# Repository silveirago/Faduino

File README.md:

# Faduino

The Faduino is a DIY MIDI controller inspired in the Presonus Faderport. It has one motorized fader, a rotary encoder and several silicone buttons, plus two PCBs. One PCB contains all the pads, which are triggered by the silicone buttons, addressable LEDs, a multiplexer, and some other stuff.
It can control natively any DAW, because it works with the MCU - or Mackie - Protocol, so it can work even in Pro Tools. With its motorized fader, rotary encoder, and LED buttons, you can change the track and the parameters in DAW get updated in the controller, moving the motorized fader, changing LEDs, etc.
With the Faduino you can control any channel strip, transport, and many other things in the DAW!

Complete Tutorial: Nerd Musician Pro (all the courses): https://go.musiconerd.com/nerd-musician-pro
Tutorialo Completo (Português): Fazendo Música com Arduino: https://go.musiconerd.com/fazendo-musica-com-arduino
Watch the YT video: https://youtu.be/M8krxn_5pIs

by Gustavo Silveira
gustavosilveira@musiconerd.com

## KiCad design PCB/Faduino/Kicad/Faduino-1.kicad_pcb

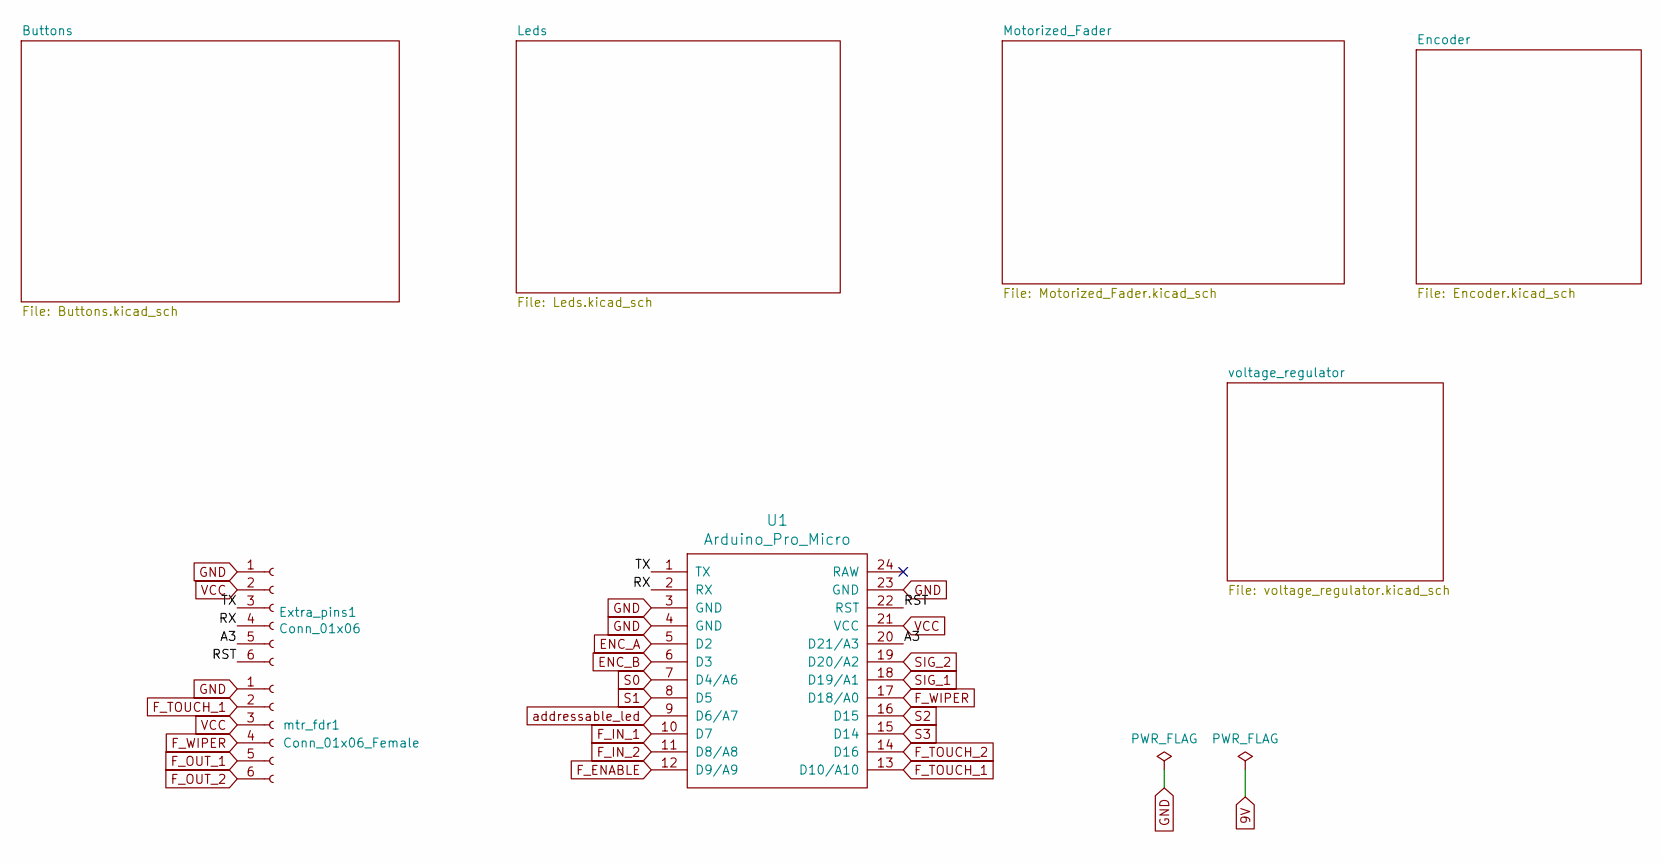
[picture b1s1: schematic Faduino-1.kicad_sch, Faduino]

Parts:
Extra_pins1: Conn_01x06; PinSocket_1x06_P2.54mm_Vertical
U1: Arduino_Pro_Micro; ArduinoProMicro
mtr_fdr1: Conn_01x06_Female; IDC-Header_2x03_P2.54mm_Vertical

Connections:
/A3: Extra_pins1.5, U1.20 (D21/A3)
/RST: Extra_pins1.6, U1.22 (RST)
/RX: Extra_pins1.4, U1.2 (RX)
/TX: Extra_pins1.3, U1.1 (TX)
ENC_A: U1.5 (D2); also elsewhere on the board
ENC_B: U1.6 (D3); also elsewhere on the board
F_ENABLE: U1.12 (D9/A9); also elsewhere on the board
F_IN_1: U1.10 (D7); also elsewhere on the board
F_IN_2: U1.11 (D8/A8); also elsewhere on the board
F_TOUCH_1: U1.13 (D10/A10), mtr_fdr1.2; also elsewhere on the board
F_TOUCH_2: U1.14 (D16); also elsewhere on the board
F_WIPER: U1.17 (D18/A0), mtr_fdr1.4; also elsewhere on the board
GND: Extra_pins1.1, U1.3 (GND), U1.4 (GND), U1.23 (GND), mtr_fdr1.1; also elsewhere on the board
S0: U1.7 (D4/A6); also elsewhere on the board
S1: U1.8 (D5); also elsewhere on the board
S2: U1.16 (D15); also elsewhere on the board
S3: U1.15 (D14); also elsewhere on the board
SIG_1: U1.18 (D19/A1); also elsewhere on the board
SIG_2: U1.19 (D20/A2); also elsewhere on the board
VCC: Extra_pins1.2, U1.21 (VCC), mtr_fdr1.3; also elsewhere on the board
addressable_led: U1.9 (D6/A7); also elsewhere on the board

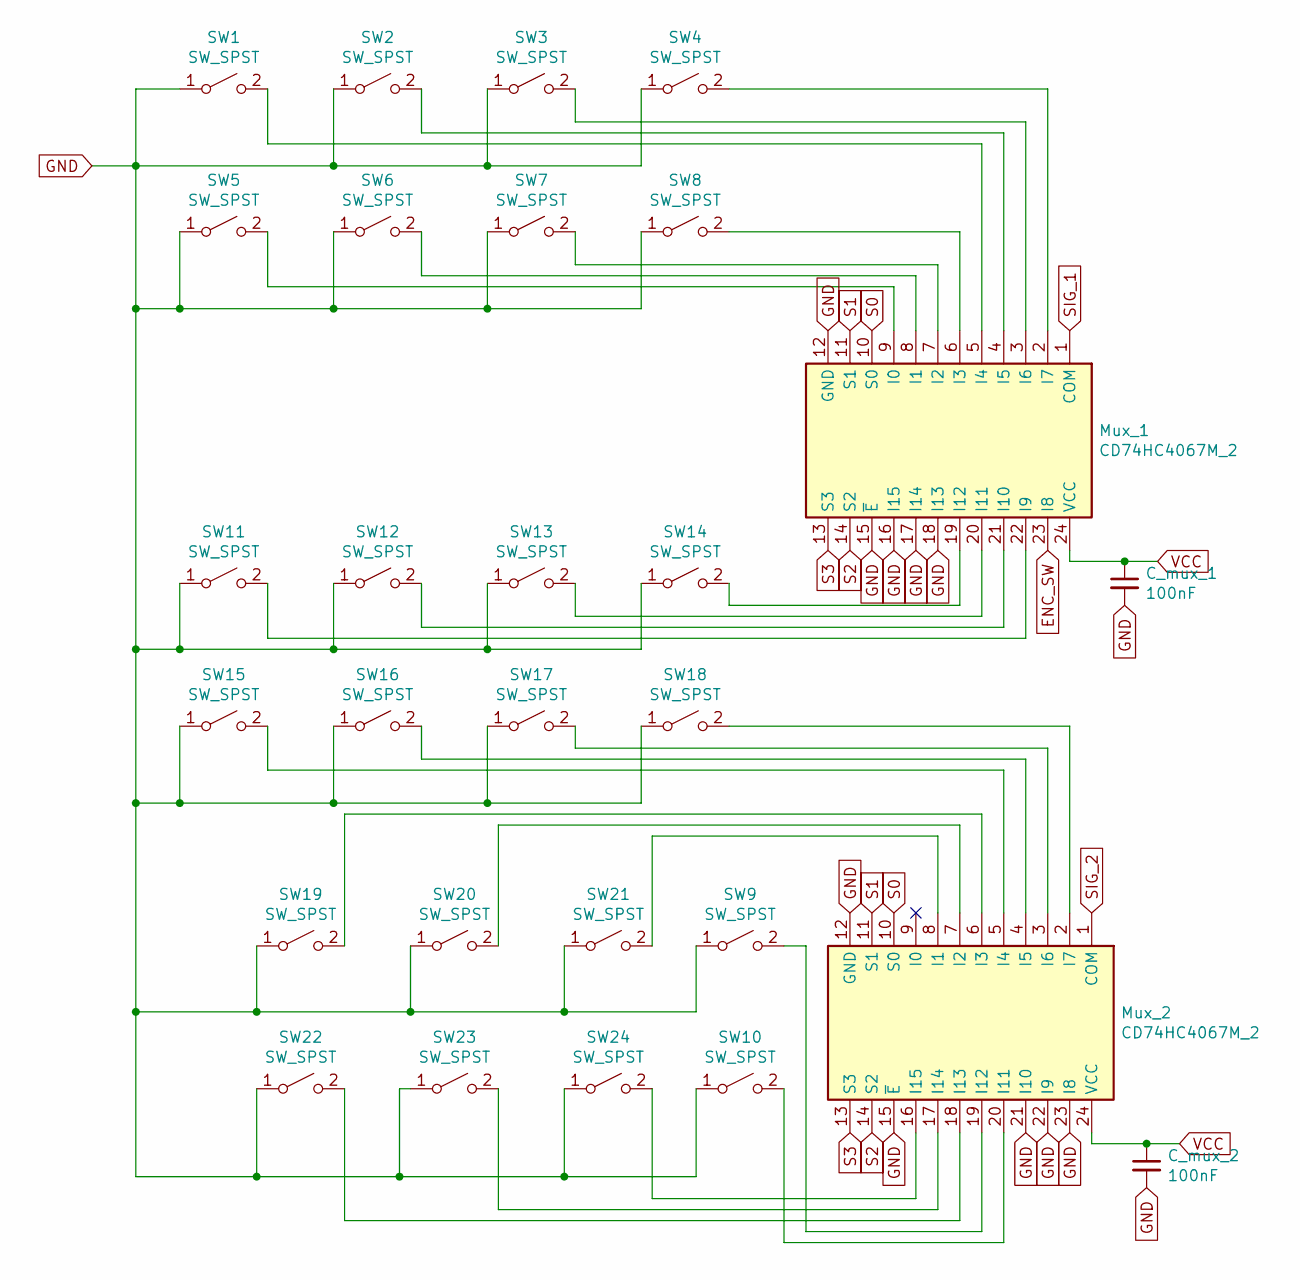
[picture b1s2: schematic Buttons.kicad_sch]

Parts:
C_mux_1, C_mux_2: 100nF; C_0603_1608Metric; LCSC Part Number C14663
Mux_1, Mux_2: CD74HC4067M_2; SSOP-24_5.3x8.2mm_P0.65mm; LCSC Part Number C98457
SW1, SW2, SW3, SW4, SW5, SW6, SW7, SW8, SW9, SW10, SW11, SW12, SW13, SW14, SW15, SW16, SW17, SW18, SW19, SW20, SW21, SW22, SW23, SW24: SW_SPST; BUTTONPAD-1x1

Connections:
ENC_SW: Mux_1.23 (I8); also elsewhere on the board
GND: C_mux_1.2, C_mux_2.2, Mux_1.12 (GND), Mux_1.15 (~E), Mux_1.16 (I15), Mux_1.17 (I14), Mux_1.18 (I13), Mux_2.12 (GND), Mux_2.15 (~E), Mux_2.21 (I10), Mux_2.22 (I9), Mux_2.23 (I8), SW1.1 (A), SW2.1 (A), SW3.1 (A), SW4.1 (A), SW5.1 (A), SW6.1 (A), SW7.1 (A), SW8.1 (A), SW9.1 (A), SW10.1 (A), SW11.1 (A), SW12.1 (A), SW13.1 (A), SW14.1 (A), SW15.1 (A), SW16.1 (A), SW17.1 (A), SW18.1 (A), SW19.1 (A), SW20.1 (A), SW21.1 (A), SW22.1 (A), SW23.1 (A), SW24.1 (A); also elsewhere on the board
unnamed: Mux_1.2 (I7), SW4.2 (B)
unnamed: Mux_1.3 (I6), SW3.2 (B)
unnamed: Mux_1.4 (I5), SW2.2 (B)
unnamed: Mux_1.5 (I4), SW1.2 (B)
unnamed: Mux_1.6 (I3), SW8.2 (B)
unnamed: Mux_1.7 (I2), SW7.2 (B)
unnamed: Mux_1.8 (I1), SW6.2 (B)
unnamed: Mux_1.9 (I0), SW5.2 (B)
unnamed: Mux_1.19 (I12), SW14.2 (B)
unnamed: Mux_1.20 (I11), SW13.2 (B)
unnamed: Mux_1.21 (I10), SW12.2 (B)
unnamed: Mux_1.22 (I9), SW11.2 (B)
unnamed: Mux_2.2 (I7), SW18.2 (B)
unnamed: Mux_2.3 (I6), SW17.2 (B)
unnamed: Mux_2.4 (I5), SW16.2 (B)
unnamed: Mux_2.5 (I4), SW15.2 (B)
unnamed: Mux_2.6 (I3), SW19.2 (B)
unnamed: Mux_2.7 (I2), SW20.2 (B)
unnamed: Mux_2.8 (I1), SW21.2 (B)
unnamed: Mux_2.16 (I15), SW24.2 (B)
unnamed: Mux_2.17 (I14), SW23.2 (B)
unnamed: Mux_2.18 (I13), SW22.2 (B)
unnamed: Mux_2.19 (I12), SW9.2 (B)
unnamed: Mux_2.20 (I11), SW10.2 (B)
S0: Mux_1.10 (S0), Mux_2.10 (S0); also elsewhere on the board
S1: Mux_1.11 (S1), Mux_2.11 (S1); also elsewhere on the board
S2: Mux_1.14 (S2), Mux_2.14 (S2); also elsewhere on the board
S3: Mux_1.13 (S3), Mux_2.13 (S3); also elsewhere on the board
SIG_1: Mux_1.1 (COM); also elsewhere on the board
SIG_2: Mux_2.1 (COM); also elsewhere on the board
VCC: C_mux_1.1, C_mux_2.1, Mux_1.24 (VCC), Mux_2.24 (VCC); also elsewhere on the board

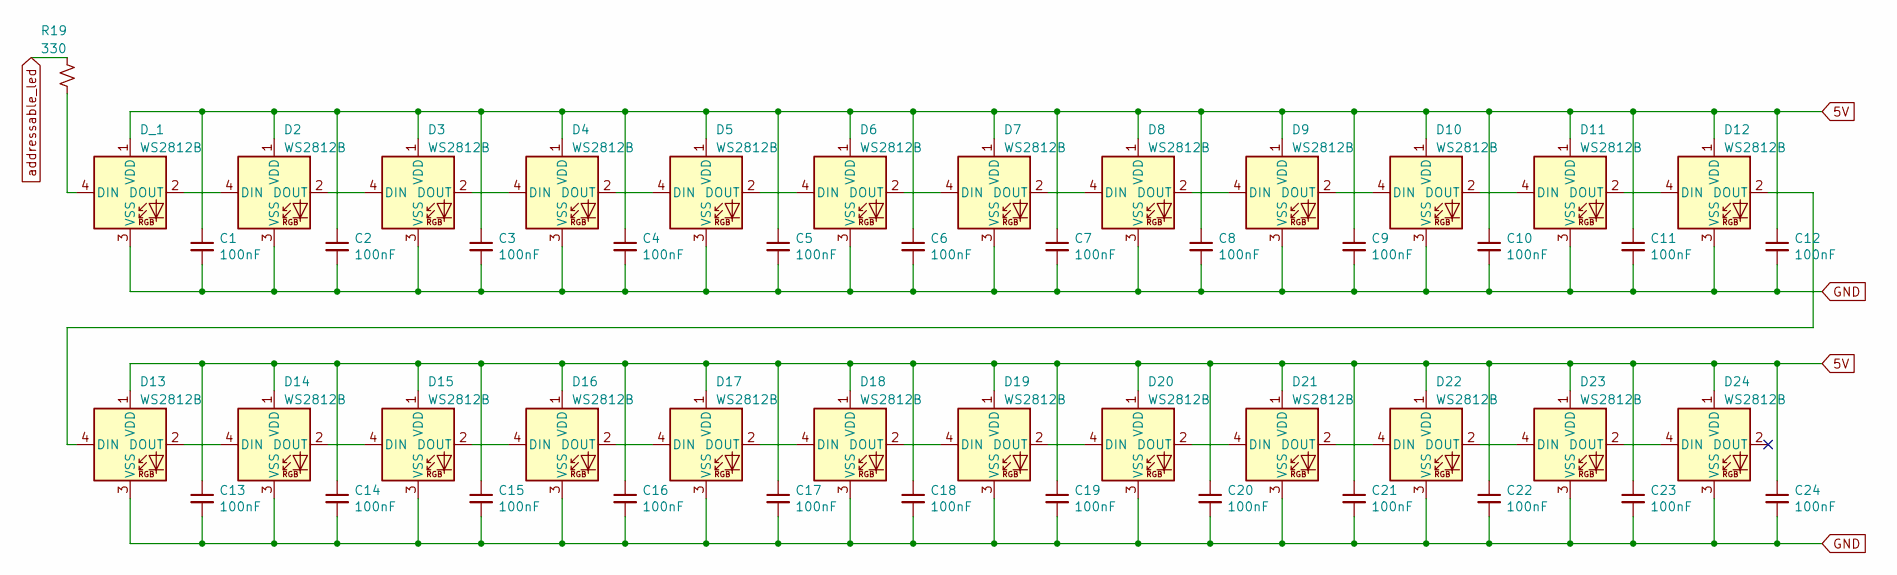
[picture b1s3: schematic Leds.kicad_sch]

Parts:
C1, C2, C3, C4, C5, C6, C7, C8, C9, C10, C11, C12, C13, C14, C15, C16, C17, C18, C19, C20, C21, C22, C23, C24: 100nF; C_0603_1608Metric; LCSC Part Number C14663
D2, D3, D4, D5, D6, D7, D8, D9, D10, D11, D12, D13, D14, D15, D16, D17, D18, D19, D20, D21, D22, D23, D24: WS2812B; WS2812B-mini-V3-2; LCSC Part Number C114583
D_1: WS2812B; WS2812B-mini-V3; LCSC Part Number C114583
R19: 330; R_0603_1608Metric; LCSC Part Number C23138

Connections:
5V: C1.1, C2.1, C3.1, C4.1, C5.1, C6.1, C7.1, C8.1, C9.1, C10.1, C11.1, C12.1, C13.1, C14.1, C15.1, C16.1, C17.1, C18.1, C19.1, C20.1, C21.1, C22.1, C23.1, C24.1, D2.1 (VDD), D3.1 (VDD), D4.1 (VDD), D5.1 (VDD), D6.1 (VDD), D7.1 (VDD), D8.1 (VDD), D9.1 (VDD), D10.1 (VDD), D11.1 (VDD), D12.1 (VDD), D13.1 (VDD), D14.1 (VDD), D15.1 (VDD), D16.1 (VDD), D17.1 (VDD), D18.1 (VDD), D19.1 (VDD), D20.1 (VDD), D21.1 (VDD), D22.1 (VDD), D23.1 (VDD), D24.1 (VDD), D_1.1 (VDD); also elsewhere on the board
GND: C1.2, C2.2, C3.2, C4.2, C5.2, C6.2, C7.2, C8.2, C9.2, C10.2, C11.2, C12.2, C13.2, C14.2, C15.2, C16.2, C17.2, C18.2, C19.2, C20.2, C21.2, C22.2, C23.2, C24.2, D2.3 (VSS), D3.3 (VSS), D4.3 (VSS), D5.3 (VSS), D6.3 (VSS), D7.3 (VSS), D8.3 (VSS), D9.3 (VSS), D10.3 (VSS), D11.3 (VSS), D12.3 (VSS), D13.3 (VSS), D14.3 (VSS), D15.3 (VSS), D16.3 (VSS), D17.3 (VSS), D18.3 (VSS), D19.3 (VSS), D20.3 (VSS), D21.3 (VSS), D22.3 (VSS), D23.3 (VSS), D24.3 (VSS), D_1.3 (VSS); also elsewhere on the board
unnamed: D2.2 (DOUT), D3.4 (DIN)
unnamed: D2.4 (DIN), D_1.2 (DOUT)
unnamed: D3.2 (DOUT), D4.4 (DIN)
unnamed: D4.2 (DOUT), D5.4 (DIN)
unnamed: D5.2 (DOUT), D6.4 (DIN)
unnamed: D6.2 (DOUT), D7.4 (DIN)
unnamed: D7.2 (DOUT), D8.4 (DIN)
unnamed: D8.2 (DOUT), D9.4 (DIN)
unnamed: D10.2 (DOUT), D11.4 (DIN)
unnamed: D9.2 (DOUT), D10.4 (DIN)
unnamed: D11.2 (DOUT), D12.4 (DIN)
unnamed: D12.2 (DOUT), D13.4 (DIN)
unnamed: D13.2 (DOUT), D14.4 (DIN)
unnamed: D14.2 (DOUT), D15.4 (DIN)
unnamed: D15.2 (DOUT), D16.4 (DIN)
unnamed: D16.2 (DOUT), D17.4 (DIN)
unnamed: D17.2 (DOUT), D18.4 (DIN)
unnamed: D18.2 (DOUT), D19.4 (DIN)
unnamed: D19.2 (DOUT), D20.4 (DIN)
unnamed: D20.2 (DOUT), D21.4 (DIN)
unnamed: D21.2 (DOUT), D22.4 (DIN)
unnamed: D22.2 (DOUT), D23.4 (DIN)
unnamed: D23.2 (DOUT), D24.4 (DIN)
unnamed: D_1.4 (DIN), R19.2
addressable_led: R19.1; also elsewhere on the board

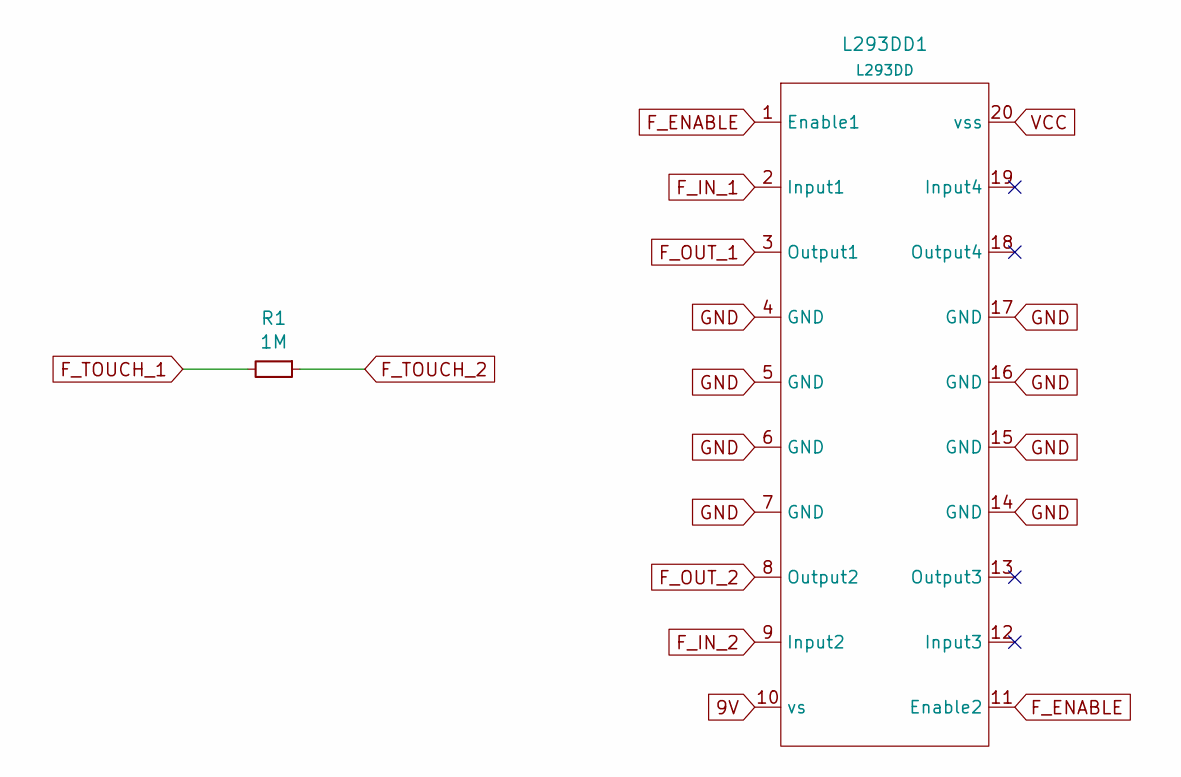
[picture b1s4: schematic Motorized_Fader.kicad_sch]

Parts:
L293DD1: L293DD; SOP-20_7.5x12.8mm_P1.27mm; LCSC C5199946
R1: 1M; R_0603_1608Metric; LCSC Part Number C22935

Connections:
9V: L293DD1.10 (vs); also elsewhere on the board
F_ENABLE: L293DD1.1 (Enable1), L293DD1.11 (Enable2); also elsewhere on the board
F_IN_1: L293DD1.2 (Input1); also elsewhere on the board
F_IN_2: L293DD1.9 (Input2); also elsewhere on the board
F_OUT_1: L293DD1.3 (Output1); also elsewhere on the board
F_OUT_2: L293DD1.8 (Output2); also elsewhere on the board
F_TOUCH_1: R1.2; also elsewhere on the board
F_TOUCH_2: R1.1; also elsewhere on the board
GND: L293DD1.4 (GND), L293DD1.5 (GND), L293DD1.6 (GND), L293DD1.7 (GND), L293DD1.14 (GND), L293DD1.15 (GND), L293DD1.16 (GND), L293DD1.17 (GND); also elsewhere on the board
VCC: L293DD1.20 (vss); also elsewhere on the board

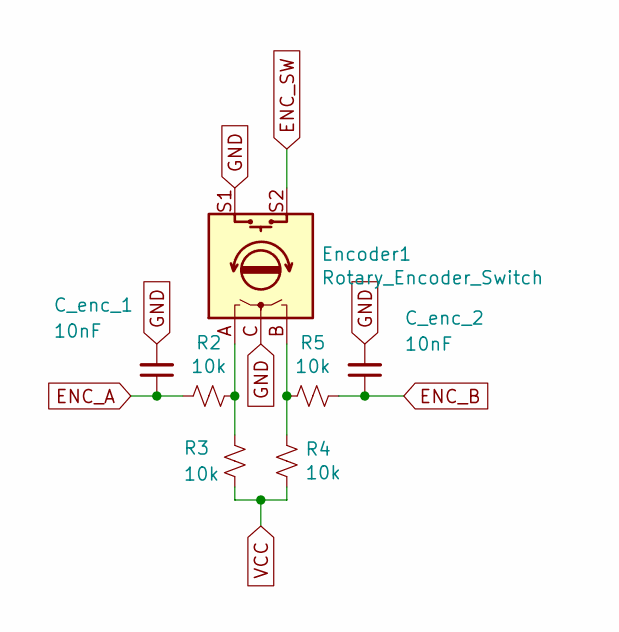
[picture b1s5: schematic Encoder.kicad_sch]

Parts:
C_enc_1, C_enc_2: 10nF; C_0603_1608Metric; LCSC Part Number C57112
Encoder1: Rotary_Encoder_Switch; RotaryEncoder_Alps_EC11E-Switch_Vertical_H20mm_CircularMoun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
R2, R3, R4, R5: 10k; R_0603_1608Metric; LCSC Part Number C25804

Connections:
ENC_A: C_enc_1.1, R2.2; also elsewhere on the board
ENC_B: C_enc_2.1, R5.1; also elsewhere on the board
ENC_SW: Encoder1.S2; also elsewhere on the board
GND: C_enc_1.2, C_enc_2.2, Encoder1.C, Encoder1.S1; also elsewhere on the board
unnamed: Encoder1.A, R2.1, R3.1
unnamed: Encoder1.B, R4.1, R5.2
VCC: R3.2, R4.2; also elsewhere on the board

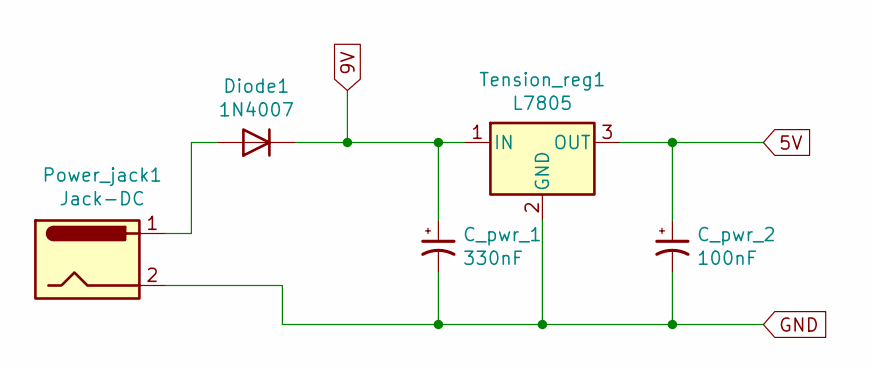
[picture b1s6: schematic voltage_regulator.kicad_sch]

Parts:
C_pwr_1: 330nF; C_0603_1608Metric; LCSC Part Number C1615
C_pwr_2: 100nF; C_0603_1608Metric; LCSC Part Number C14663
Diode1: 1N4007; D_SMA_Handsoldering; LCSC Part Number C727081
Power_jack1: Jack-DC; BarrelJack_Horizontal
Tension_reg1: L7805; TO-263-2; LCSC C310413

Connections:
5V: C_pwr_2.1, Tension_reg1.3 (OUT); also elsewhere on the board
9V: C_pwr_1.1, Diode1.1 (K), Tension_reg1.1 (IN); also elsewhere on the board
GND: C_pwr_1.2, C_pwr_2.2, Power_jack1.2, Tension_reg1.2 (GND); also elsewhere on the board
unnamed: Diode1.2 (A), Power_jack1.1

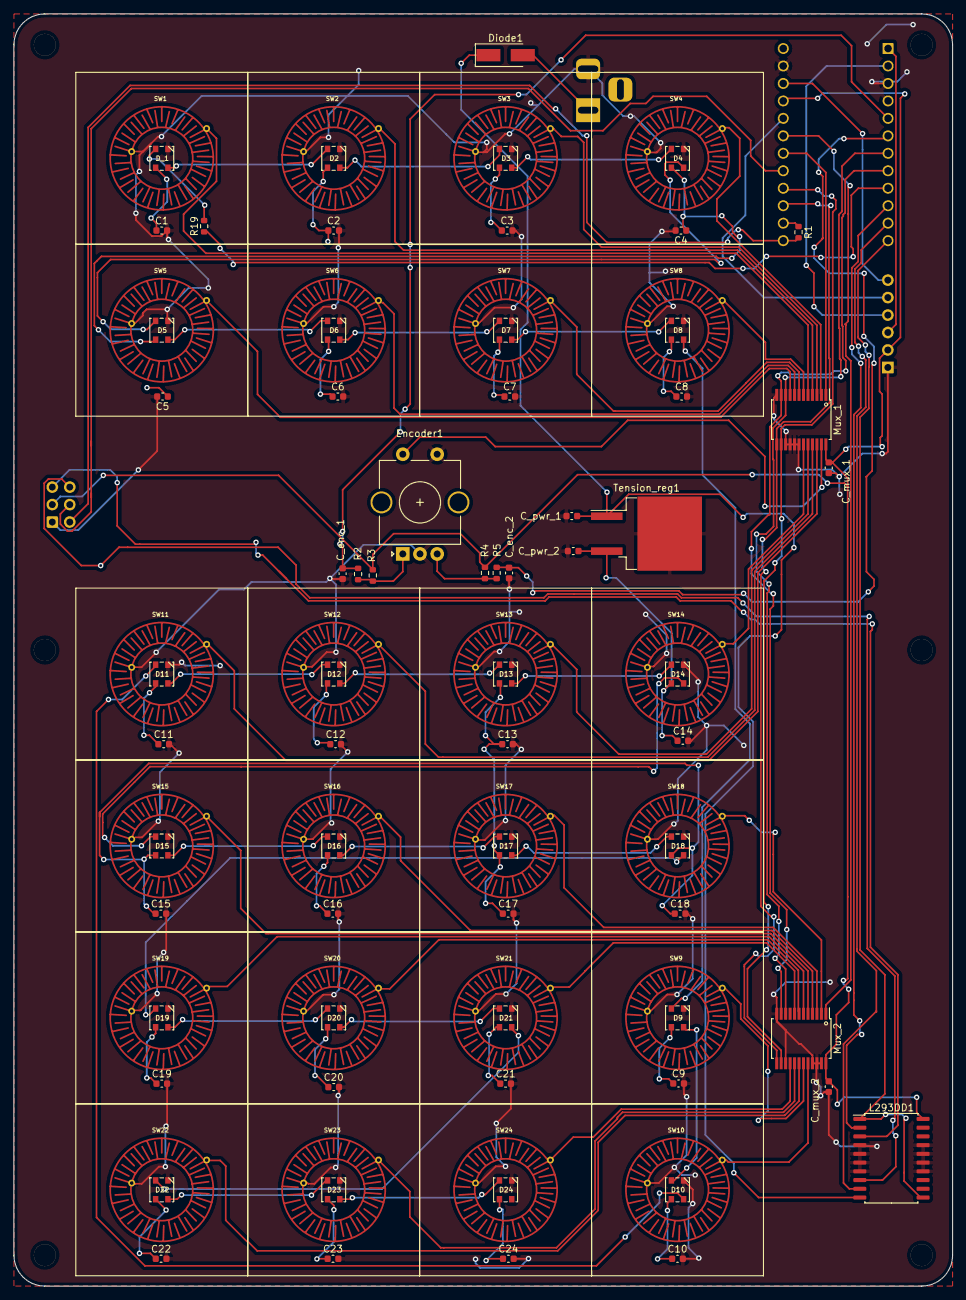
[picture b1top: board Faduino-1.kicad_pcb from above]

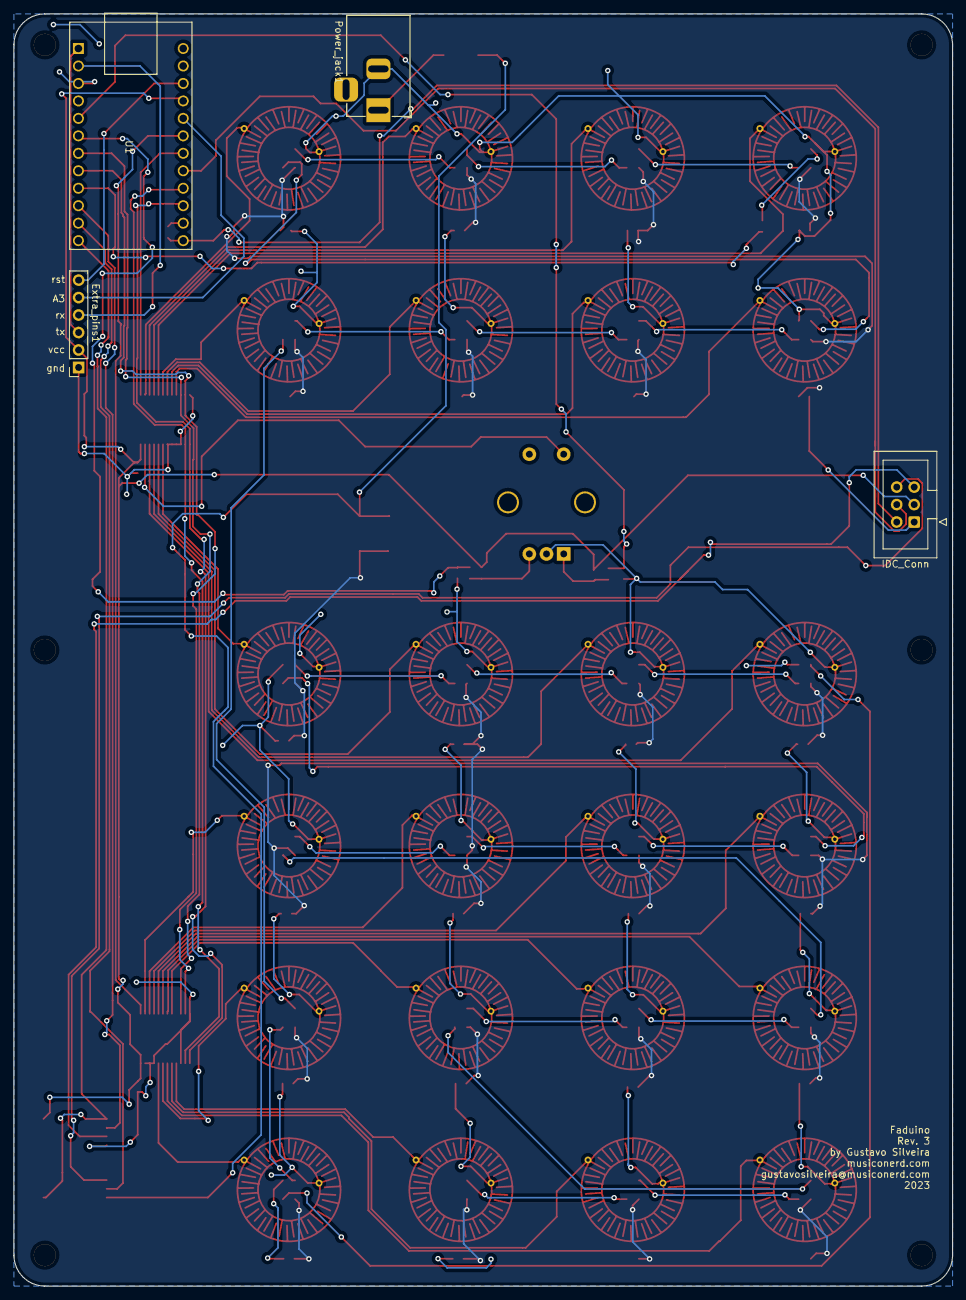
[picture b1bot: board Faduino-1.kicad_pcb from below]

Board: 2 copper layers, 136.5 x 185.0 mm, 94 parts (4 on the bottom side), 77 nets.

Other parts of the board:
IDC_Conn: Conn_01x06_Female; IDC-Header_2x03_P2.54mm_Vertical

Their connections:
F_OUT_1: IDC_Conn.5; also elsewhere on the board
F_OUT_2: IDC_Conn.6; also elsewhere on the board
F_TOUCH_1: IDC_Conn.2; also elsewhere on the board
F_WIPER: IDC_Conn.4; also elsewhere on the board
GND: IDC_Conn.1; also elsewhere on the board
VCC: IDC_Conn.3; also elsewhere on the board

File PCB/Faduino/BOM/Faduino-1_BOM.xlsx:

Comment | Designator | Footprint | LCSC Part #
100nF Unpolarized capacitor, small symbol | C1,C2,C3,C4,C5,C6,C7,C8,C9,C10,C11,C12,C13,C14,C15,C16,C17,C18,C19,C20,C21,C22,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 | C_0603_1608Metric | C14663
100nF Unpolarized capacitor, small symbol | C_mux_1,C_mux_2 | C_0603_1608Metric | C14663
100nF | C_pwr_2 | C_0603_1608Metric | C14663
L7805 Positive 1.5A 35V Linear Regulator, Fixed Output 5V, TO-220/TO-263/TO-252 | Tension_reg1 | TO-263-2 | C15077
330nF | C_pwr_1 | C_0603_1608Metric | C1615
1M Resistor, small symbol | R1 | R_0603_1608Metric | C22935
330 Resistor, small US symbol | R19 | R_0603_1608Metric | C22935
10k Resistor, small US symbol | R2,R3,R4,R5 | R_0603_1608Metric | C25804
L293DD | L293DD1 | SOP-20_7.5x12.8mm_P1.27mm | C5199946
WS2812B RGB LED with integrated controller | D2,D3,D4,D5,D6,D7,D8,D9,D10,D11,D12,D13,D14,D15,D16,D17,D18,D19,D20,D21,D22,D23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 | WS2812B-mini-V3-2 | C527089
WS2812B RGB LED with integrated controller | D_1 | WS2812B-mini-V3 | C527089
10nF Unpolarized capacitor, small symbol | C_enc_1,C_enc_2 | C_0603_1608Metric | C57112
1N4007 1000V 1A General Purpose Rectifier Diode, DO-41 | Diode1 | D_SMA_Handsoldering | C727081
CD74HC4067M_2 | Mux_1,Mux_2 | SSOP-24_5.3x8.2mm_P0.65mm | C97702

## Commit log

2023-10-19 code updated
2023-10-23 enclisure and PCB files added
